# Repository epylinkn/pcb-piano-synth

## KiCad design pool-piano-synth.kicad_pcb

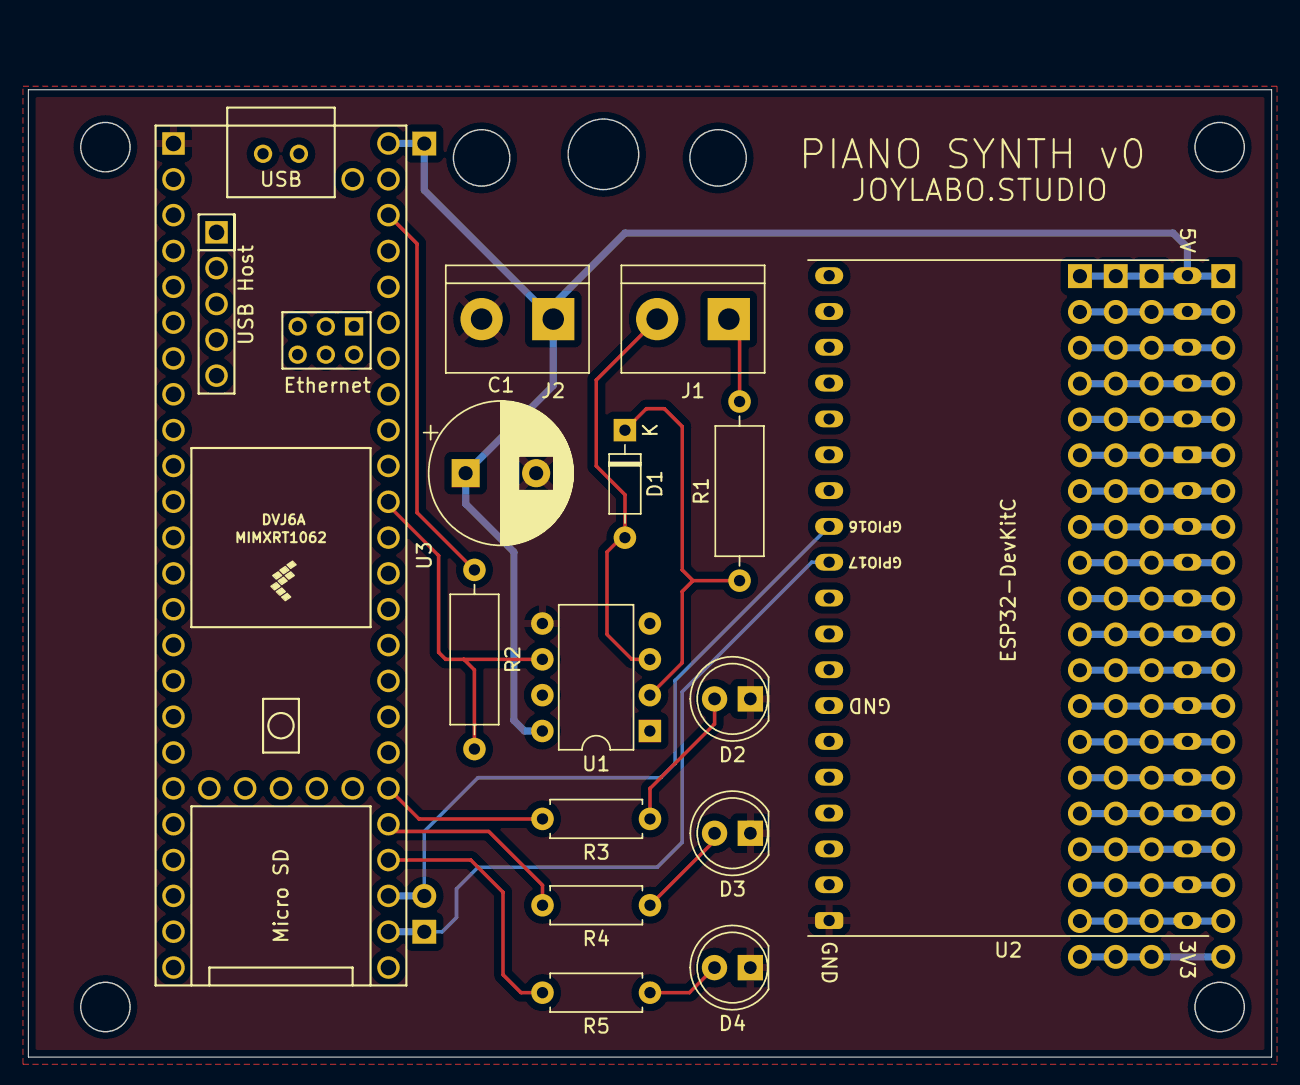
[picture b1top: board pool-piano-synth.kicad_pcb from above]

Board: 2 copper layers, 88.1 x 72.9 mm, 21 parts (0 on the bottom side), 34 nets.

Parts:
C1: 0.1uF; CP_Radial_D10.0mm_P5.00mm
D1: 1N4148; D_DO-35_SOD27_P7.62mm_Horizontal
D2: GRN; LED_D5.0mm
D3: YEL; LED_D5.0mm
D4: RED; LED_D5.0mm
J1, J2: Screw_Terminal_01x02; TerminalBlock_bornier-2_P5.08mm
J3: Conn_01x01_Male; PinHeader_1x01_P2.54mm_Vertical
J4, J5, J6, J7: Conn_01x20_Male; PinHeader_1x20_P2.54mm_Vertical
J8: Conn_01x02_Male; PinHeader_1x02_P2.54mm_Vertical
R1: 220; R_Axial_DIN0309_L9.0mm_D3.2mm_P12.70mm_Horizontal
R2: 470; R_Axial_DIN0309_L9.0mm_D3.2mm_P12.70mm_Horizontal
R3: 15; R_Axial_DIN0207_L6.3mm_D2.5mm_P7.62mm_Horizontal
R4, R5: 68; R_Axial_DIN0207_L6.3mm_D2.5mm_P7.62mm_Horizontal
U1: 6N138; DIP-8_W7.62mm
U2: ESP32-DevKitC
U3: Teensy4.1; Teensy41

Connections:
+3V3: R2.1, U3.46 (3V3)
GND: C1.2, D2.1 (K), D3.1 (K), D4.1 (K), J2.2, U1.5 (GND), U2.38 (GND), U3.1 (GND)
unnamed: D1.1 (K), R1.1, U1.2 (C1)
unnamed: D1.2 (A), J1.2, U1.3 (C2)
unnamed: D2.2 (A), R3.1
unnamed: D3.2 (A), R4.1
unnamed: D4.2 (A), R5.1
unnamed: J1.1, R1.2
unnamed: J4.20, J5.20, J6.20, J7.20
unnamed: R2.2, U1.6 (VO2), U3.38 (16_A2_RX4_SCL1)
unnamed: R3.2, U3.30 (38_CS1_IN1)
unnamed: R4.2, U3.29 (37_CS)
unnamed: R5.2, U3.28 (36_CS)
unnamed: J4.19, J5.19, J6.19, J7.19, U2.1 (3V3)
unnamed: J4.18, J5.18, J6.18, J7.18, U2.2 (CHIP_PU)
unnamed: J4.17, J5.17, J6.17, J7.17, U2.3 (SENSOR_VP/GPIO36/ADC1_CH0)
unnamed: J4.16, J5.16, J6.16, J7.16, U2.4 (SENSOR_VN/GPIO39/ADC1_CH3)
unnamed: J4.15, J5.15, J6.15, J7.15, U2.5 (VDET_1/GPIO34/ADC1_CH6)
unnamed: J4.14, J5.14, J6.14, J7.14, U2.6 (VDET_2/GPIO35/ADC1_CH7)
unnamed: J4.13, J5.13, J6.13, J7.13, U2.7 (32K_XP/GPIO32/ADC1_CH4)
unnamed: J4.12, J5.12, J6.12, J7.12, U2.8 (32K_XN/GPIO33/ADC1_CH5)
unnamed: J4.11, J5.11, J6.11, J7.11, U2.9 (DAC_1/ADC2_CH8/GPIO25)
unnamed: J4.10, J5.10, J6.10, J7.10, U2.10 (DAC_2/ADC2_CH9/GPIO26)
unnamed: J4.9, J5.9, J6.9, J7.9, U2.11 (ADC2_CH7/GPIO27)
unnamed: J4.8, J5.8, J6.8, J7.8, U2.12 (MTMS/GPIO14/ADC2_CH6)
unnamed: J4.7, J5.7, J6.7, J7.7, U2.13 (*MTDI/GPIO12/ADC2_CH5)
unnamed: J4.6, J5.6, J6.6, J7.6, U2.14 (GND)
unnamed: J4.5, J5.5, J6.5, J7.5, U2.15 (MTCK/GPIO13/ADC2_CH4)
unnamed: J4.4, J5.4, J6.4, J7.4, U2.16 (SD_DATA2/GPIO9)
unnamed: J4.3, J5.3, J6.3, J7.3, U2.17 (SD_DATA3/GPIO10)
unnamed: J4.2, J5.2, J6.2, J7.2, U2.18 (CMD)
unnamed: J8.2, U2.27 (GPIO16), U3.27 (35_TX8)
unnamed: J8.1, U2.28 (GPIO17), U3.26 (34_RX8)
VCC: C1.1, J2.1, J3.1, J4.1, J5.1, J6.1, J7.1, U1.8 (VCC), U2.19 (5V), U3.48 (VIN)

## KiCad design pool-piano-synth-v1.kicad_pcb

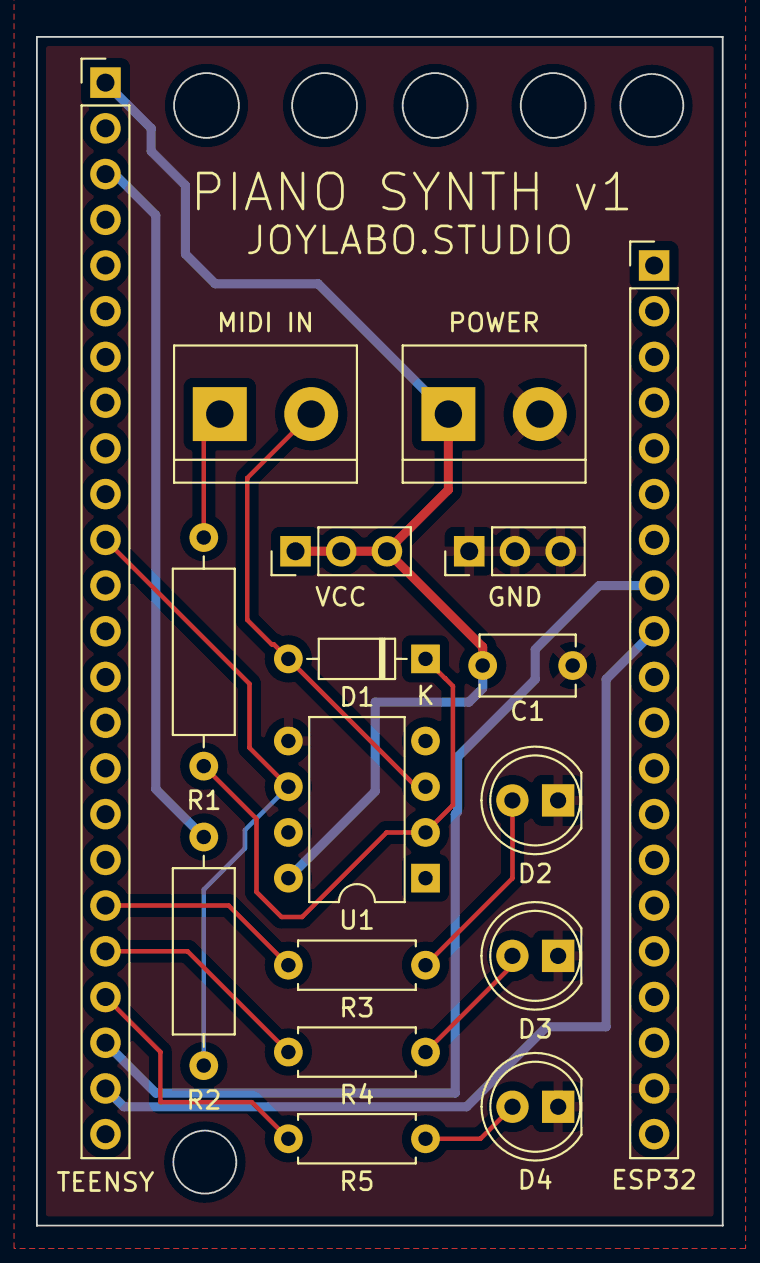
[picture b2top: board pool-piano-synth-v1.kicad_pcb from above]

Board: 2 copper layers, 38.1 x 66.0 mm, 17 parts (0 on the bottom side), 15 nets.

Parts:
C1: 0.1uF; C_Disc_D5.1mm_W3.2mm_P5.00mm
D1: 1N4148; D_DO-35_SOD27_P7.62mm_Horizontal
D2: GRN; LED_D5.0mm
D3: YEL; LED_D5.0mm
D4: RED; LED_D5.0mm
ESP32: Conn_01x20_Male; PinHeader_1x20_P2.54mm_Vertical
GND: Conn_01x03_Male; PinHeader_1x03_P2.54mm_Vertical
MIDI IN: Screw_Terminal_01x02; TerminalBlock_bornier-2_P5.08mm
POWER: Screw_Terminal_01x02; TerminalBlock_bornier-2_P5.08mm
R1: 220; R_Axial_DIN0309_L9.0mm_D3.2mm_P12.70mm_Horizontal
R2: 470; R_Axial_DIN0309_L9.0mm_D3.2mm_P12.70mm_Horizontal
R3: 15; R_Axial_DIN0207_L6.3mm_D2.5mm_P7.62mm_Horizontal
R4, R5: 68; R_Axial_DIN0207_L6.3mm_D2.5mm_P7.62mm_Horizontal
TEENSY: Conn_01x24_Male; PinHeader_1x24_P2.54mm_Vertical
U1: 6N138; DIP-8_W7.62mm
VCC: Conn_01x03_Male; PinHeader_1x03_P2.54mm_Vertical

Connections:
+3V3: R2.1, TEENSY.3
GND: C1.2, D2.1 (K), D3.1 (K), D4.1 (K), ESP32.19, GND.1, GND.2, GND.3, POWER.2, U1.5 (GND)
unnamed: D1.1 (K), R1.1, U1.2 (C1)
unnamed: D1.2 (A), MIDI IN.2, U1.3 (C2)
unnamed: D2.2 (A), R3.1
unnamed: D3.2 (A), R4.1
unnamed: D4.2 (A), R5.1
unnamed: MIDI IN.1, R1.2
unnamed: R2.2, TEENSY.11, U1.6 (VO2)
unnamed: ESP32.8, TEENSY.22
unnamed: ESP32.9, TEENSY.23
unnamed: R5.2, TEENSY.21
unnamed: R4.2, TEENSY.20
unnamed: R3.2, TEENSY.19
VCC: C1.1, POWER.1, TEENSY.1, U1.8 (VCC), VCC.1, VCC.2, VCC.3

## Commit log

2022-05-25 Good looking schematic + board without traces
2022-05-26 v0: ready to print
    - add traces, zones, better footprints
2022-05-26 v1: printing at oshpark
    - smaller footprint = less $$$
